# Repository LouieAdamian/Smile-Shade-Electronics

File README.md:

# Smile Shade Electronics

PCB layout for Smile Shade

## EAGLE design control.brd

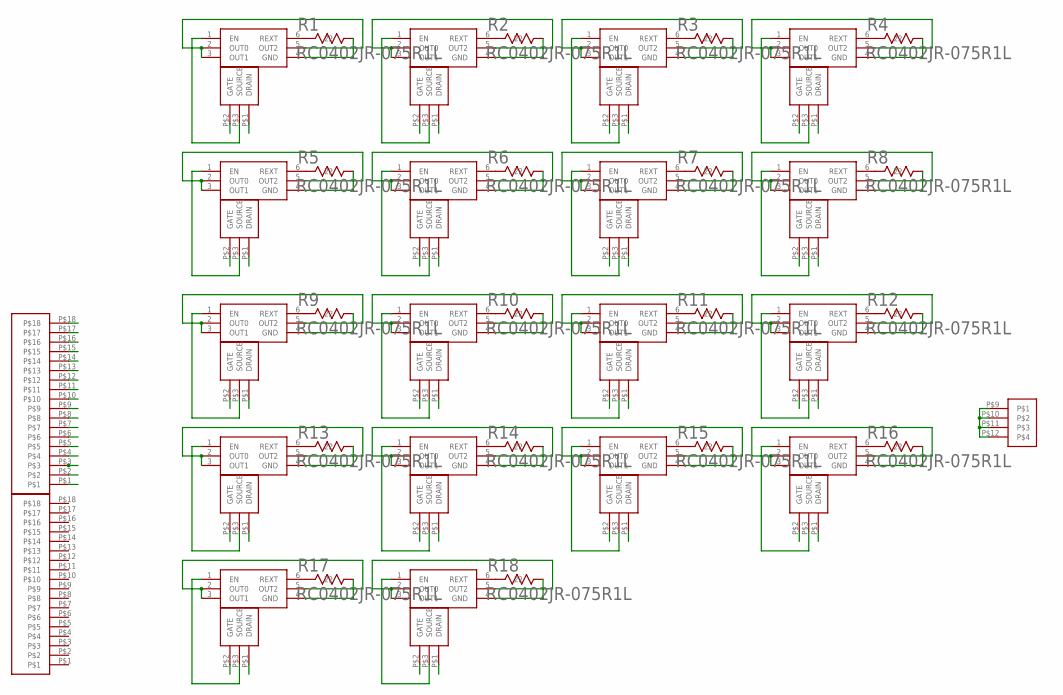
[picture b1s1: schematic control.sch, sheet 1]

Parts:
R1, R2, R3, R4, R5, R6, R7, R8, R9, R10, R11, R12, R13, R14, R15, R16, R17, R18: RC0402JR-075R1L; RC0402N
U$2, U$4, U$6, U$8, U$10, U$12, U$14, U$16, U$18, U$20, U$22, U$24, U$26, U$28, U$30, U$32, U$34, U$40: BCR420UW6-7; SOT26
U$3, U$5, U$7, U$9, U$11, U$13, U$15, U$17, U$19, U$21, U$23, U$25, U$27, U$29, U$31, U$33, U$35, U$38: 2N7002P; SOT23
U$39: SFV4R-3STBE1HLF
U$44, U$80: SFV18R-3STBE1HLF

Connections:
GND: R1.1 (11), U$2.4 (GND), U$38.P$1 (DRAIN), U$39.P$9, U$39.P$10, U$39.P$11, U$39.P$12; also elsewhere on the board
GND1: R2.1 (11), U$3.P$1 (DRAIN), U$4.4 (GND)
GND2: R3.1 (11), U$5.P$1 (DRAIN), U$6.4 (GND)
GND3: R4.1 (11), U$7.P$1 (DRAIN), U$8.4 (GND)
GND4: R5.1 (11), U$9.P$1 (DRAIN), U$10.4 (GND)
GND5: R6.1 (11), U$11.P$1 (DRAIN), U$12.4 (GND)
GND6: R7.1 (11), U$13.P$1 (DRAIN), U$14.4 (GND)
GND7: R8.1 (11), U$15.P$1 (DRAIN), U$16.4 (GND)
GND8: R9.1 (11), U$17.P$1 (DRAIN), U$18.4 (GND)
GND9: R10.1 (11), U$19.P$1 (DRAIN), U$20.4 (GND)
GND10: R11.1 (11), U$21.P$1 (DRAIN), U$22.4 (GND)
GND11: R12.1 (11), U$23.P$1 (DRAIN), U$24.4 (GND)
GND12: R13.1 (11), U$25.P$1 (DRAIN), U$26.4 (GND)
GND13: R14.1 (11), U$27.P$1 (DRAIN), U$28.4 (GND)
GND14: R15.1 (11), U$29.P$1 (DRAIN), U$30.4 (GND)
GND15: R16.1 (11), U$31.P$1 (DRAIN), U$32.4 (GND)
GND16: R17.1 (11), U$33.P$1 (DRAIN), U$34.4 (GND)
GND17: R18.1 (11), U$35.P$1 (DRAIN), U$40.4 (GND)
LEDSTR_1: U$2.2 (OUT0), U$2.3 (OUT1), U$2.5 (OUT2), U$44.P$1
LEDSTR_2: U$4.2 (OUT0), U$4.3 (OUT1), U$4.5 (OUT2), U$44.P$2
LEDSTR_3: U$6.2 (OUT0), U$6.3 (OUT1), U$6.5 (OUT2), U$44.P$3
LEDSTR_4: U$8.2 (OUT0), U$8.3 (OUT1), U$8.5 (OUT2), U$44.P$4
LEDSTR_5: U$44.P$7
LEDSTR_6: U$44.P$6
LEDSTR_7: U$44.P$5
LEDSTR_8: U$44.P$8
LEDSTR_9: U$44.P$9
LEDSTR_10: U$44.P$10
LEDSTR_11: U$44.P$11
LEDSTR_12: U$44.P$12
LEDSTR_13: U$44.P$13
LEDSTR_14: U$44.P$14
LEDSTR_15: U$44.P$15
LEDSTR_16: U$44.P$16
LEDSTR_17: U$44.P$18
LEDSTR_18: U$44.P$17
LEDSTR_19: U$10.2 (OUT0), U$10.3 (OUT1), U$10.5 (OUT2)
LEDSTR_20: U$12.2 (OUT0), U$12.3 (OUT1), U$12.5 (OUT2)
LEDSTR_21: U$14.2 (OUT0), U$14.3 (OUT1), U$14.5 (OUT2)
LEDSTR_22: U$16.2 (OUT0), U$16.3 (OUT1), U$16.5 (OUT2)
LEDSTR_23: U$18.2 (OUT0), U$18.3 (OUT1), U$18.5 (OUT2)
LEDSTR_24: U$20.2 (OUT0), U$20.3 (OUT1), U$20.5 (OUT2)
LEDSTR_25: U$22.2 (OUT0), U$22.3 (OUT1), U$22.5 (OUT2)
LEDSTR_26: U$24.2 (OUT0), U$24.3 (OUT1), U$24.5 (OUT2)
LEDSTR_27: U$26.2 (OUT0), U$26.3 (OUT1), U$26.5 (OUT2)
LEDSTR_28: U$28.2 (OUT0), U$28.3 (OUT1), U$28.5 (OUT2)
LEDSTR_29: U$30.2 (OUT0), U$30.3 (OUT1), U$30.5 (OUT2)
LEDSTR_30: U$32.2 (OUT0), U$32.3 (OUT1), U$32.5 (OUT2)
LEDSTR_31: U$34.2 (OUT0), U$34.3 (OUT1), U$34.5 (OUT2)
LEDSTR_32: U$40.2 (OUT0), U$40.3 (OUT1), U$40.5 (OUT2)
unnamed: R1.2 (22), U$2.6 (REXT)
unnamed: U$2.1 (EN), U$38.P$3 (SOURCE)
unnamed: U$3.P$3 (SOURCE), U$4.1 (EN)
unnamed: R2.2 (22), U$4.6 (REXT)
unnamed: U$5.P$3 (SOURCE), U$6.1 (EN)
unnamed: R3.2 (22), U$6.6 (REXT)
unnamed: U$7.P$3 (SOURCE), U$8.1 (EN)
unnamed: R4.2 (22), U$8.6 (REXT)
unnamed: U$9.P$3 (SOURCE), U$10.1 (EN)
unnamed: R5.2 (22), U$10.6 (REXT)
unnamed: U$11.P$3 (SOURCE), U$12.1 (EN)
unnamed: R6.2 (22), U$12.6 (REXT)
unnamed: U$13.P$3 (SOURCE), U$14.1 (EN)
unnamed: R7.2 (22), U$14.6 (REXT)
unnamed: U$15.P$3 (SOURCE), U$16.1 (EN)
unnamed: R8.2 (22), U$16.6 (REXT)
unnamed: U$17.P$3 (SOURCE), U$18.1 (EN)
unnamed: R9.2 (22), U$18.6 (REXT)
unnamed: U$19.P$3 (SOURCE), U$20.1 (EN)
unnamed: R10.2 (22), U$20.6 (REXT)
unnamed: U$21.P$3 (SOURCE), U$22.1 (EN)
unnamed: R11.2 (22), U$22.6 (REXT)
unnamed: U$23.P$3 (SOURCE), U$24.1 (EN)
unnamed: R12.2 (22), U$24.6 (REXT)
unnamed: U$25.P$3 (SOURCE), U$26.1 (EN)
unnamed: R13.2 (22), U$26.6 (REXT)
unnamed: U$27.P$3 (SOURCE), U$28.1 (EN)
unnamed: R14.2 (22), U$28.6 (REXT)
unnamed: U$29.P$3 (SOURCE), U$30.1 (EN)
unnamed: R15.2 (22), U$30.6 (REXT)
unnamed: U$31.P$3 (SOURCE), U$32.1 (EN)
unnamed: R16.2 (22), U$32.6 (REXT)
unnamed: U$33.P$3 (SOURCE), U$34.1 (EN)
unnamed: R17.2 (22), U$34.6 (REXT)
unnamed: U$35.P$3 (SOURCE), U$40.1 (EN)
unnamed: R18.2 (22), U$40.6 (REXT)
ZN0: U$38.P$2 (GATE); also elsewhere on the board
ZN16: U$3.P$2 (GATE)
ZN17: U$5.P$2 (GATE)
ZN18: U$7.P$2 (GATE)
ZN19: U$9.P$2 (GATE)
ZN20: U$11.P$2 (GATE)
ZN21: U$13.P$2 (GATE)
ZN22: U$15.P$2 (GATE)
ZN23: U$17.P$2 (GATE)
ZN24: U$19.P$2 (GATE)
ZN25: U$21.P$2 (GATE)
ZN26: U$23.P$2 (GATE)
ZN27: U$25.P$2 (GATE)
ZN28: U$27.P$2 (GATE)
ZN29: U$29.P$2 (GATE)
ZN30: U$31.P$2 (GATE)
ZN31: U$33.P$2 (GATE)
ZN32: U$35.P$2 (GATE)

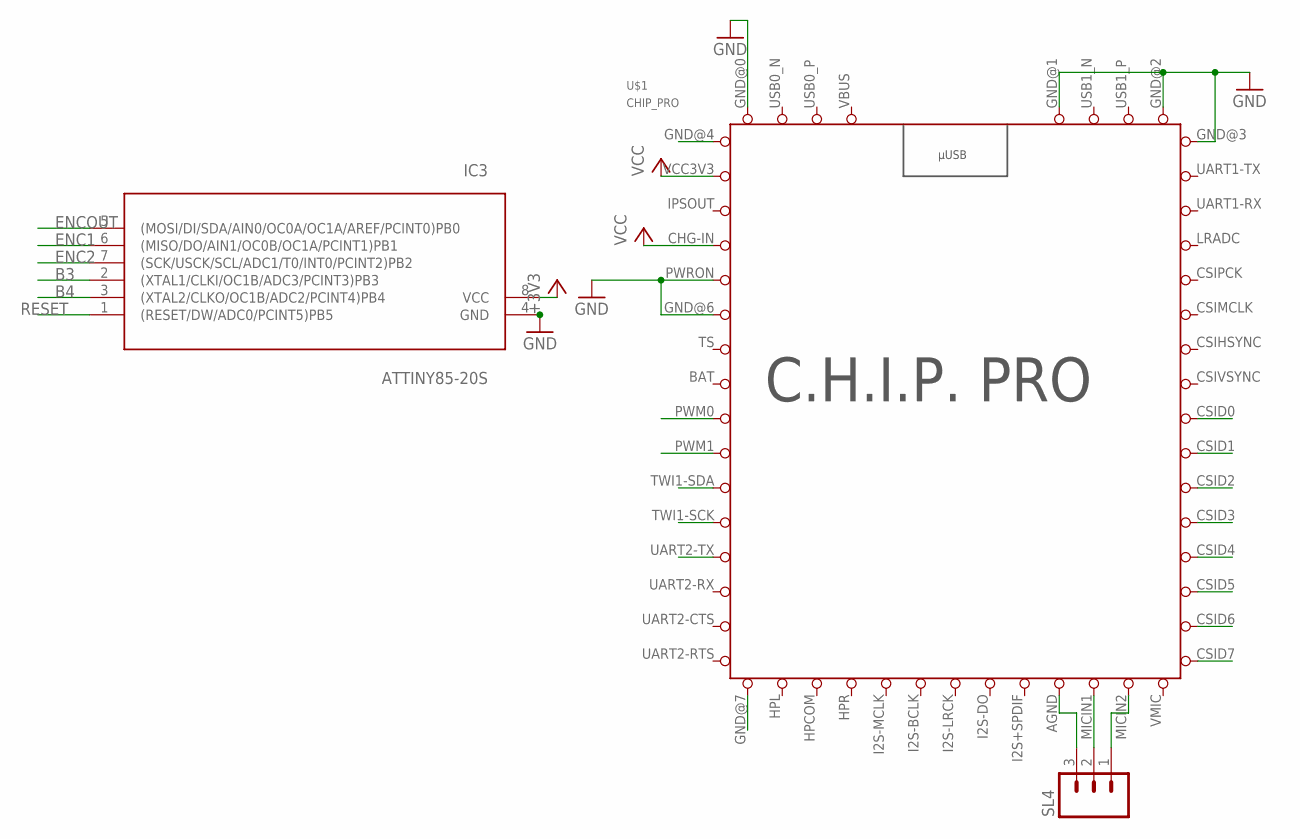
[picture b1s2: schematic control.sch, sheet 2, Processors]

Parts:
IC3: ATTINY85-20S; SOIC8
SL4: M03; 03P
U$1: CHIP_PRO

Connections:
3V3: U$1.VCC3V3; also elsewhere on the board
+3V3: IC3.8 (VCC)
B3: IC3.2 ((XTAL1/CLKI/OC1B/ADC3/PCINT3)PB3)
B4: IC3.3 ((XTAL2/CLKO/OC1B/ADC2/PCINT4)PB4)
DIR1A: U$1.CSID4; also elsewhere on the board
DIR1B: U$1.CSID5; also elsewhere on the board
DIR2A: U$1.CSID6; also elsewhere on the board
DIR2B: U$1.CSID7; also elsewhere on the board
ENC1: IC3.6 ((MISO/DO/AIN1/OC0B/OC1A/PCINT1)PB1); also elsewhere on the board
ENC2: IC3.7 ((SCK/USCK/SCL/ADC1/T0/INT0/PCINT2)PB2); also elsewhere on the board
ENCOUT: IC3.5 ((MOSI/DI/SDA/AIN0/OC0A/OC1A/AREF/PCINT0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), U$1.UART2-TX
ENDSTOP0: U$1.CSID0; also elsewhere on the board
ENDSTOP1: U$1.CSID1; also elsewhere on the board
ENDSTOP2: U$1.CSID2; also elsewhere on the board
ENDSTOP3: U$1.CSID3; also elsewhere on the board
GND: IC3.4 (GND), U$1.GND@0 (GND), U$1.GND@1 (GND), U$1.GND@2 (GND), U$1.GND@3 (GND), U$1.GND@4 (GND), U$1.GND@6 (GND), U$1.GND@7 (GND), U$1.PWRON; also elsewhere on the board
IPSOUT: U$1.IPSOUT
M1: U$1.PWM0; also elsewhere on the board
M2: U$1.PWM1; also elsewhere on the board
unnamed: SL4.3, U$1.AGND
unnamed: SL4.2, U$1.MICIN1
unnamed: SL4.1, U$1.MICIN2
RESET: IC3.1 ((RESET/DW/ADC0/PCINT5)PB5)
SCK: U$1.TWI1-SCK; also elsewhere on the board
SDA: U$1.TWI1-SDA; also elsewhere on the board
VBUS: U$1.VBUS
VIN: U$1.CHG-IN; also elsewhere on the board

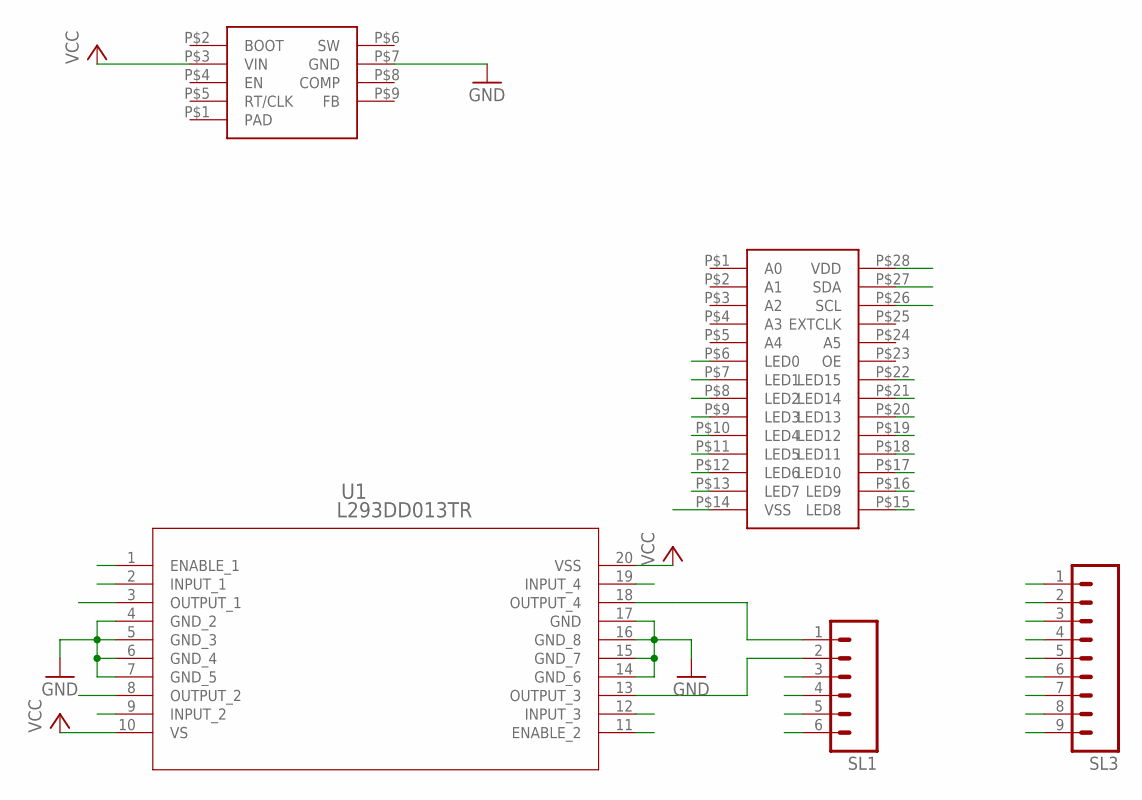
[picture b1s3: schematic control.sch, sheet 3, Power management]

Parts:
SL1: M06; 06P
SL3: M09; 09P
U1: L293DD013TR; SO-20
U$37: PCA9685PW/Q900; SOT361-1
U$42: TPS54560DDAR; 8-S-POWERPAD

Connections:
3V3: SL1.3, SL3.7; also elsewhere on the board
5V: U1.20 (VSS), U$37.P$28 (VDD)
DIR1A: U1.2 (INPUT_1); also elsewhere on the board
DIR1B: U1.9 (INPUT_2); also elsewhere on the board
DIR2A: U1.19 (INPUT_4); also elsewhere on the board
DIR2B: U1.12 (INPUT_3); also elsewhere on the board
ENC1: SL1.5; also elsewhere on the board
ENC2: SL1.6; also elsewhere on the board
ENDSTOP0: SL3.3; also elsewhere on the board
ENDSTOP1: SL3.4; also elsewhere on the board
ENDSTOP2: SL3.5; also elsewhere on the board
ENDSTOP3: SL3.6; also elsewhere on the board
GND: SL1.4, SL3.2, U1.4 (GND_2), U1.5 (GND_3), U1.6 (GND_4), U1.7 (GND_5), U1.14 (GND_6), U1.15 (GND_7), U1.16 (GND_8), U1.17 (GND), U$37.P$14 (VSS), U$42.P$7 (GND); also elsewhere on the board
M1: U1.1 (ENABLE_1); also elsewhere on the board
M1A: SL3.8, U1.3 (OUTPUT_1)
M1B: SL3.9, U1.8 (OUTPUT_2)
M2: U1.11 (ENABLE_2); also elsewhere on the board
M2A: SL1.1, U1.18 (OUTPUT_4)
M2B: SL1.2, U1.13 (OUTPUT_3)
SCK: U$37.P$26 (SCL); also elsewhere on the board
SDA: U$37.P$27 (SDA); also elsewhere on the board
VCC: U1.10 (VS)
VIN: SL3.1, U$42.P$3 (VIN); also elsewhere on the board
ZN0: U$37.P$13 (LED7); also elsewhere on the board
ZN1: U$37.P$12 (LED6)
ZN2: U$37.P$11 (LED5)
ZN3: U$37.P$10 (LED4)
ZN4: U$37.P$9 (LED3)
ZN5: U$37.P$8 (LED2)
ZN6: U$37.P$7 (LED1)
ZN7: U$37.P$6 (LED0)
ZN8: U$37.P$15 (LED8)
ZN9: U$37.P$16 (LED9)
ZN10: U$37.P$17 (LED10)
ZN11: U$37.P$18 (LED11)
ZN12: U$37.P$19 (LED12)
ZN13: U$37.P$20 (LED13)
ZN14: U$37.P$21 (LED14)
ZN15: U$37.P$22 (LED15)

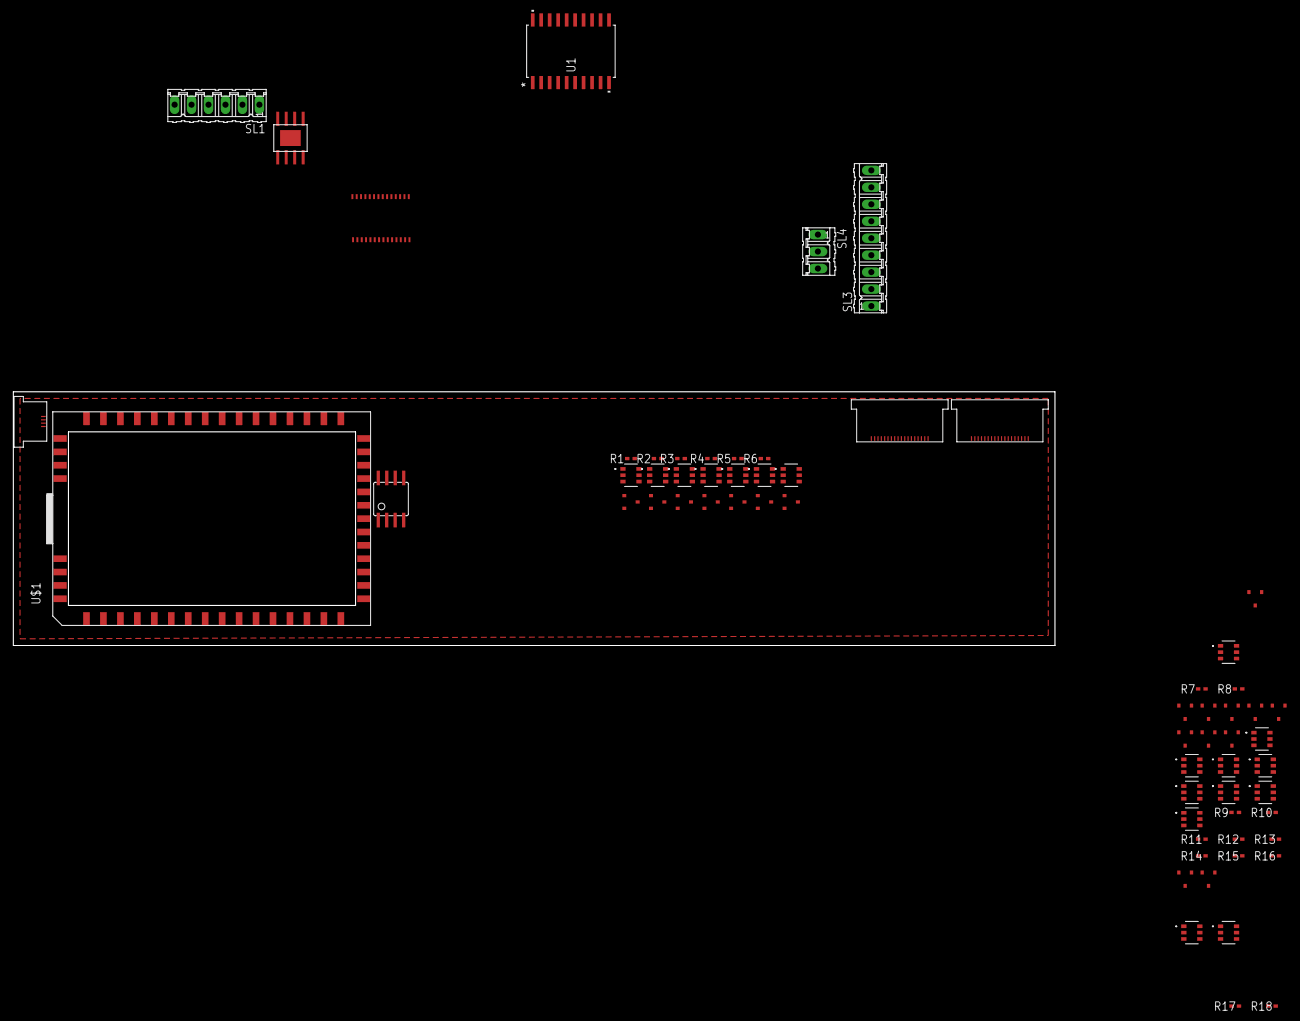
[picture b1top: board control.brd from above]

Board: 2 copper layers, 156.0 x 38.0 mm, 65 parts (0 on the bottom side), 98 nets.

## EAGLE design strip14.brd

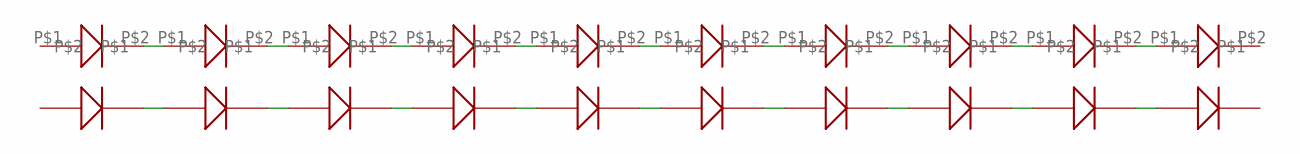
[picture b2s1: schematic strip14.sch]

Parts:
U$1, U$2, U$3, U$4, U$5, U$6, U$7, U$8, U$9, U$10: JDSTS2.EM-HRHT-XX52-1
U$11, U$12, U$13, U$14, U$15, U$16, U$17, U$18, U$19, U$20: BXEN-40E-11M-3A-00-0-0

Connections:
unnamed: U$1.3V, U$2.GND
unnamed: U$2.3V, U$3.GND
unnamed: U$3.3V, U$4.GND
unnamed: U$4.3V, U$5.GND
unnamed: U$5.3V, U$6.GND
unnamed: U$6.3V, U$7.GND
unnamed: U$7.3V, U$8.GND
unnamed: U$8.3V, U$9.GND
unnamed: U$9.3V, U$10.GND
unnamed: U$19.P$2, U$20.P$1
unnamed: U$18.P$2, U$19.P$1
unnamed: U$17.P$2, U$18.P$1
unnamed: U$16.P$2, U$17.P$1
unnamed: U$15.P$2, U$16.P$1
unnamed: U$11.P$2, U$12.P$1
unnamed: U$12.P$2, U$13.P$1
unnamed: U$13.P$2, U$14.P$1
unnamed: U$14.P$2, U$15.P$1

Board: 2 copper layers, 20 parts (0 on the bottom side), 18 nets, no tracks yet.

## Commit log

2016-11-09 adds dimmer and h bridge
2016-11-13 starts adding rectifier
2016-11-30 adds rectifir
2016-11-30 adds MT7688AN library
2017-01-17 deletes old LED controller
2017-01-19 Adds new LED
2017-01-20 adds H-bridge
2017-01-20 adds h bridge wirirng
2017-01-27 adds LED driver
2017-02-09 adds PWM
2017-02-10 adds flex connector
2017-02-10 new layout
2017-02-11 Revert "adds flex connector"
    This reverts commit c0465f8f5036756819879aef16fe9e16a98b933a.
2017-02-11 Revert "new layout"
    This reverts commit 1a592baa1633963169f0595642268c9a5a9af5d5.
2017-02-11 adds gitignore
2017-02-11 add compacted layout
2017-02-11 Revert "Merged branch new-layout into new-layout"
    This reverts commit 740985ea758dd0223a13bad39dafdbdca556afef.
2017-02-14 Revert "Merge remote-tracking branch 'refs/remotes/origin/master' into new-layout"
    This reverts commit d786cf153478cbc5e1d0f0cbdb23b775e7a3effd.
2017-02-14 adds compacted new layout
2017-02-14 adds double sided led driver layout
2017-02-15 adds trinket to desing
2017-02-15 changes to 3v3 trinket
2017-02-16 FAIL compact layout
2017-02-21 completes first ideration
2017-02-22 adds actual route
2017-02-23 fixes DRC err
2017-02-23 adds ADC input with all RDC and rounting
2017-02-23 adds gerbers
2017-02-24 fixes capacitor orientation
2017-02-27 adds new components
2017-02-27 adds new layout
2017-02-27 adds new route
2017-03-07 adds new LED driver
2017-03-27 setts up warm cool LED support
2017-03-28 Finalised-ish warm to cool dimming schematic
2017-04-06 removes excess led controllers
